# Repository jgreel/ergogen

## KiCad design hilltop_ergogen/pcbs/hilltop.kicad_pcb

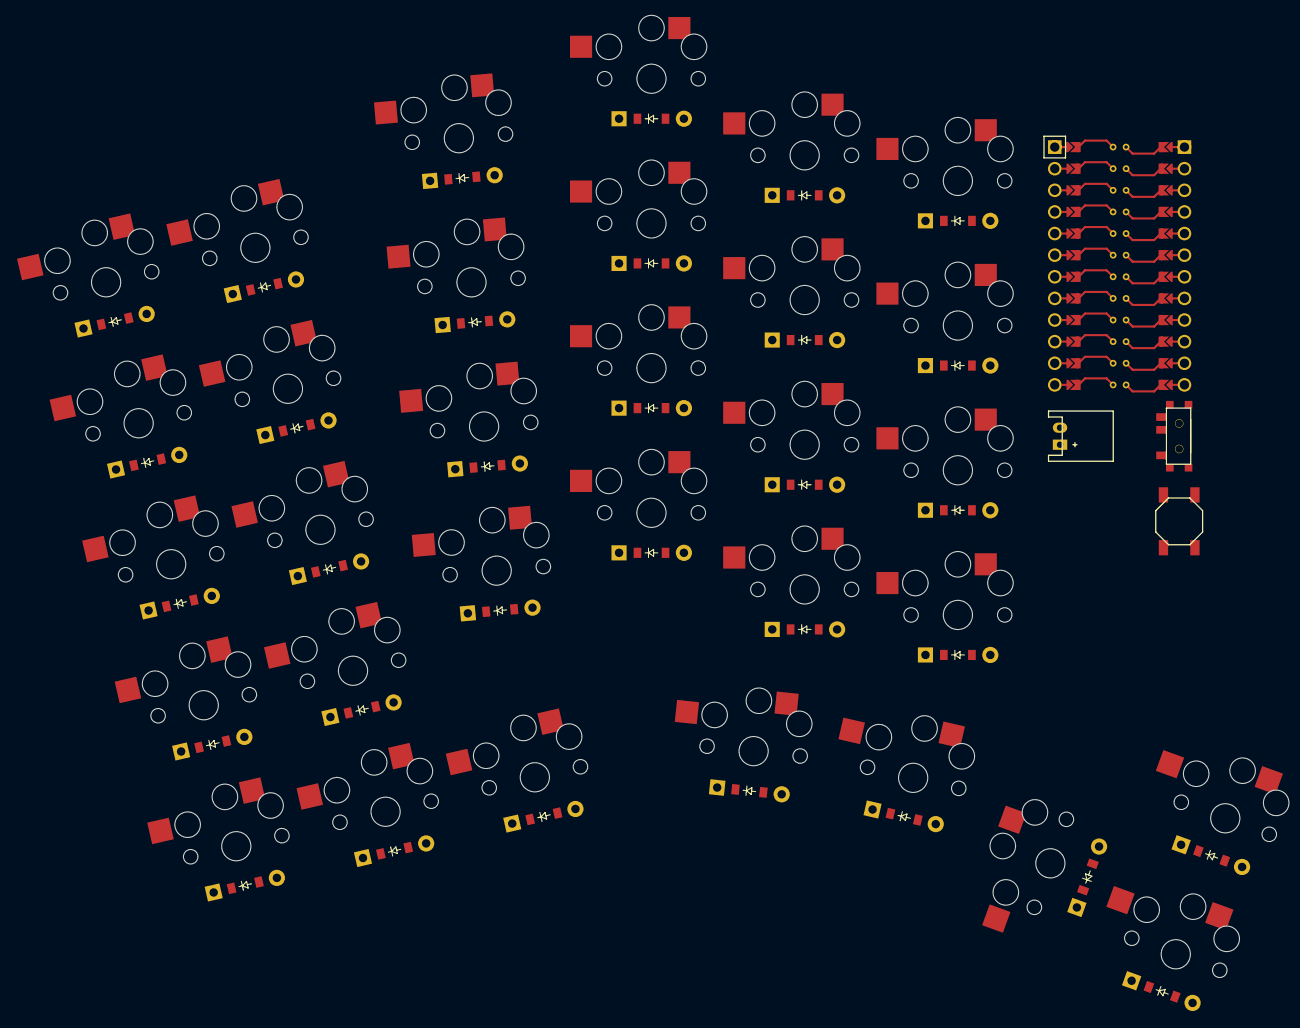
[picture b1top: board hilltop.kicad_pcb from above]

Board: 2 copper layers, 68 parts (0 on the bottom side), 7 nets, no tracks yet.

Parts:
B1: SW_TACT_ALPS_SKQGABE010
D1, D2, D3, D4, D5, D6, D7, D8, D9, D10, D11, D12, D13, D14, D15, D16, D17, D18, D19, D20, D21, D22, D23, D24, D25, D26, D27, D28, D29, D30, D31, D32: ComboDiode
JST1: JST_PH_S2B-PH-K_02x2.00mm_Angled
MCU1: ProMicro
S1, S2, S3, S4, S5, S6, S7, S8, S9, S10, S11, S12, S13, S14, S15, S16, S17, S18, S19, S20, S21, S22, S23, S24, S25, S26, S27, S28, S29, S30, S31, S32: PG1350
T1: SPDT_C128955

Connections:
BAT: JST1.1, T1.2
GND: B1.2, JST1.2, MCU1.2, MCU1.21, MCU1.22
RAW: MCU1.1, T1.1
RST: B1.1, MCU1.3
{{colrow}}: D1.1, D2.1, D3.1, D4.1, D5.1, D6.1, D7.1, D8.1, D9.1, D10.1, D11.1, D12.1, D13.1, D14.1, D15.1, D16.1, D17.1, D18.1, D19.1, D20.1, D21.1, D22.1, D23.1, D24.1, D25.1, D26.1, D27.1, D28.1, D29.1, D30.1, D31.1, D32.1
{{column_net}}: S1.2, S2.2, S3.2, S4.2, S5.2, S6.2, S7.2, S8.2, S9.2, S10.2, S11.2, S12.2, S13.2, S14.2, S15.2, S16.2, S17.2, S18.2, S19.2, S20.2, S21.2, S22.2, S23.2, S24.2, S25.2, S26.2, S27.2, S28.2, S29.2, S30.2, S31.2, S32.2
{{row_net}}: D1.2, D2.2, D3.2, D4.2, D5.2, D6.2, D7.2, D8.2, D9.2, D10.2, D11.2, D12.2, D13.2, D14.2, D15.2, D16.2, D17.2, D18.2, D19.2, D20.2, D21.2, D22.2, D23.2, D24.2, D25.2, D26.2, D27.2, D28.2, D29.2, D30.2, D31.2, D32.2, S1.1, S2.1, S3.1, S4.1, S5.1, S6.1, S7.1, S8.1, S9.1, S10.1, S11.1, S12.1, S13.1, S14.1, S15.1, S16.1, S17.1, S18.1, S19.1, S20.1, S21.1, S22.1, S23.1, S24.1, S25.1, S26.1, S27.1, S28.1, S29.1, S30.1, S31.1, S32.1

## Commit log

2023-03-04 add promicro_pretty footprint
2023-03-04 update promicro pretty
2023-03-05 update config & promicro_pretty footprint
2023-03-05 fix pin numbering
